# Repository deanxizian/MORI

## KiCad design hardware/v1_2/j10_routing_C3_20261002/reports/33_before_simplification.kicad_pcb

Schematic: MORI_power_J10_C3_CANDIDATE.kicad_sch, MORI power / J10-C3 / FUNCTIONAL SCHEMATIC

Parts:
C1, C20: 100n; C_0603_1608Metric
C2: 1u 25V; C_0603_1608Metric__P3_C2
C10: Panasonic EEU-FR1C102 1000uF 16V; CP_Radial_D10.0mm_P5.00mm__P2_C10__P3_C10__P5_C10
C21, C41: 10n; C_0603_1608Metric
C30: Panasonic EEU-FR1C102 1000uF 16V; CP_Radial_D10.0mm_P5.00mm__P3_C30__P5_C30
C40: 100n; C_0603_1608Metric__P5_C40
C60: 22u / 25V / X7R; C_1210_3225Metric__P3_C60__P3R1_C60
C61: 100n / 50V / X7R; C_0603_1608Metric__P5_C61
C62, C72: 100n / 50V / X7R; C_0603_1608Metric
C63: 22u / 25V / X7R; C_1210_3225Metric__P5_C63
C64, C66, C73, C76: 22u / 25V / X7R; C_1210_3225Metric
C65: 75p / 50V / C0G; C_0603_1608Metric__P5_C65
C70: 22u / 25V / X7R; C_1210_3225Metric__P3_C70
C71: 100n / 50V / X7R; C_0603_1608Metric__P5_C71
C74: 22u / 25V / X7R; C_1210_3225Metric__P3_C74
C75: 75p / 50V / C0G; C_0603_1608Metric__P3R1_C75
D1, D20, D90: BZT52H-C10,115; D_SOD-123F
D10: B540C-13-F; D_SMC__P3_D10__P5_D10
D30: B540C-13-F; D_SMC__P5_D30
D40: BZT52H-C10,115; D_SOD-123F__P5_D40
F60: 1A / 125V / very fast; Fuse_Littelfuse-NANO2-451_453
F70: 2A / 125V / very fast; Fuse_Littelfuse-NANO2-451_453__P5_F70
H1, H2, H3, H4: M2 mounting / POSITION TBD; MountingHole_2.2mm_M2
J1: PACK AFTER 6.3A FUSE; AMASS_XT30UPB-M_1x02_P5.0mm_Vertical__P3_J1
J2: WHEEL BUCK VIN; AMASS_XT30UPB-M_1x02_P5.0mm_Vertical__P3_J2__P5_J2
J3: WHEEL BUCK 9V RETURN; AMASS_XT30UPB-M_1x02_P5.0mm_Vertical__P3R1_J3
J4: HEAD BUCK VIN; AMASS_XT30UPB-M_1x02_P5.0mm_Vertical__P2_J4__P3_J4__P3R1_J4
J5: HEAD BUCK 6V RETURN; AMASS_XT30UPB-M_1x02_P5.0mm_Vertical__P2_J5__P3_J5__P5_J5
J6: BAT_MON SERVICE / DNP; AMASS_XT30UPB-M_1x02_P5.0mm_Vertical__P3_J6__P3R1_J6; not fitted
J7: S288 L; JST_XH_B3B-XH-A_1x03_P2.50mm_Vertical__P2_J7__P3_J7__P5_J7
J8: S288 R; JST_XH_B3B-XH-A_1x03_P2.50mm_Vertical__P2_J8__P5_J8
J9: SCS0009 CHAIN; JST_XH_B3B-XH-A_1x03_P2.50mm_Vertical__P5_J9
J10: MOTION CONTROL; JST_PH_S8B-PH-K_1x08_P2.00mm_Horizontal__C2_land1p50_finish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
J11: WHEEL DUMP 5R6 EXTERNAL; AMASS_XT30UPB-M_1x02_P5.0mm_Vertical__P5R5_DUMP
J12: HEAD DUMP 10R EXTERNAL; AMASS_XT30UPB-M_1x02_P5.0mm_Vertical__P2_J12__P5_J12__P5R5_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
J13: S288 DATA; JST_PH_B2B-PH-K_1x02_P2.00mm_Vertical__P4_PH_ANNULUS
J14: HEAD DATA; JST_PH_B3B-PH-K_1x03_P2.00mm_Vertical__P4_PH_ANNULUS
J15: CHARGE INTERLOCK; JST_PH_B2B-PH-K_1x02_P2.00mm_Vertical__P4_PH_ANNULUS__P3R1_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
J16: CHARGER RAW VBUS SENSE; JST_PH_B2B-PH-K_1x02_P2.00mm_Vertical__P4_PH_ANNULUS__P3R1_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
J17: MOTION 5V OUT / 1+ 2GND; JST_PH_B2B-PH-K_1x02_P2.00mm_Vertical__P4_PH_ANNULUS
J18: CAM 5V OUT / 1+ 2GND; JST_XH_B2B-XH-A_1x02_P2.50mm_Vertical
J19: REAR MASTER / 1RETURN 2GND; JST_PH_B2B-PH-K_1x02_P2.00mm_Vertical__P4_PH_ANNULUS__P5_J19
JP60: SERVICE OFF / OPEN=ON; PinHeader_1x02_P2.54mm_Vertical__P3_JP60__P3R1_JP60
JP70: SERVICE OFF / OPEN=ON; PinHeader_1x02_P2.54mm_Vertical__P5_JP70
L60, L70: 10uH / SRP7050TA-100M; Bourns_SRP7050TA_8p4_span_2p5_gap
Q1: AO4407A; SOIC-8_3.9x4.9mm_P1.27mm__P5_Q1
Q10, Q90: AO4407A; SOIC-8_3.9x4.9mm_P1.27mm
Q11: AO3400A; SOT-23__P5_Q11
Q20, Q31, Q40: AO3400A; SOT-23
Q30: AO4407A; SOIC-8_3.9x4.9mm_P1.27mm__P5_Q30
Q50: MMBT3904LT1G; SOT-23__P5_Q50
R1, R30, R91: 10k; R_0603_1608Metric
R2: WSL2512R0100FEA 10mR 1% 1W; R_2512_6332Metric
R3, R4: 0; R_0603_1608Metric
R10: 10k; R_0603_1608Metric__P5_R10
R11: 100; R_0603_1608Metric__P5_R11
R20, R24, R40, R44: 2.2k; R_0603_1608Metric
R21: 33.2k 0.1%; R_0603_1608Metric
R22: 10k 0.1%; R_0603_1608Metric__P5_R22
R23, R43: 1M 0.1%; R_0603_1608Metric
R25: 37.4k 0.1%; R_0603_1608Metric
R26, R42, R46: 10k 0.1%; R_0603_1608Metric
R31: 100; R_0603_1608Metric__P5_R31
R41: 16.5k 0.1%; R_0603_1608Metric
R45: 18.7k 0.1%; R_0603_1608Metric__P5_R45
R50, R52: 100k 0.1%; R_0603_1608Metric
R51, R53: 27k 0.1%; R_0603_1608Metric
R54: 10k; R_0603_1608Metric__P5_R54
R55: 47k; R_0603_1608Metric
R56: 100k; R_0603_1608Metric__P5_R56
R60, R70: 100k / 0.1%; R_0603_1608Metric
R61: 13.3k / 0.1%; R_0603_1608Metric
R71: 13.3k / 0.1%; R_0603_1608Metric__P3_R71
R90: 100k; R_0603_1608Metric
TP60: +5V_MOTION; TestPoint_Pad_D1.5mm__P3_TP60
TP61: GND; TestPoint_Pad_D1.5mm__P5_TP61
TP70: +5V_CAM; TestPoint_Pad_D1.5mm__P3R1_TP70
TP71: GND; TestPoint_Pad_D1.5mm__P5_TP71
U1: INA180A1IDBVR; SOT-23-5__P5_U1
U20: LM393BDR; SOIC-8_3.9x4.9mm_P1.27mm__P5_U20
U21: TL431BIDBZR; SOT-23
U40: LM393BDR; SOIC-8_3.9x4.9mm_P1.27mm__P5_U40
U41: TL431BIDBZR; SOT-23__P5_U41
U60, U70: TPS54302DDCR; TI_DDC0006A_TPS54302

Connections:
/+3V3: C1.1, J10.1, U1.5 (VS)
/+5V_CAM: C73.1, C74.1, C75.1, J18.1 (5V_OUT), L70.2, R70.1, TP70.1
/+5V_MOTION: C63.1, C64.1, C65.1, J17.1 (5V_OUT), L60.2, R60.1, TP60.1
/ARM_Q: J10.2, Q11.1, Q31.1, R54.1
/BAT_ADC: J10.5, R50.2, R51.1
/BAT_IN: Q1.5, Q1.6, Q1.7, Q1.8, Q90.5, Q90.6, Q90.7, Q90.8
/BAT_MON: C2.1, F60.1, F70.1, J2.2 (PLUS), J4.2 (PLUS), J6.2 (PLUS), R2.2, R4.1, R50.1
/BAT_REV: D1.1, Q1.1 (SOURCE PROTECTED OUTPUT), Q1.2, Q1.3, R2.1, R3.1
/C5_BOOT: C72.1, U70.6 (BOOT)
/C5_EN: JP70.1 (EN), U70.5 (EN)
/C5_FB: C75.2, R70.2, R71.1, U70.4 (FB)
/C5_SW: C72.2, L70.1, U70.2 (SW)
/C5_VIN: C70.1, C71.1, C76.1, F70.2, U70.3 (VIN)
/CHG_BASE: Q50.1 (B), R55.2, R56.1
/CHG_N: J10.4, J15.1, Q50.3 (C)
/CURRENT_ADC: J10.7, U1.1 (OUT)
/FAULT_N: J10.3, U20.7 (OUT2), U40.7 (OUT2)
/GND: C1.2, C2.2, C10.2, C20.2, C21.2, C30.2, C40.2, C41.2, C60.2, C61.2, C63.2, C64.2, C66.2, C70.2, C71.2, C73.2, C74.2, C76.2, D20.2, D40.2, J1.1 (MINUS), J2.1 (MINUS), J3.1 (MINUS), J4.1 (MINUS), J5.1 (MINUS), J6.1 (MINUS), J7.1 (GND), J8.1 (GND), J9.1 (GND), J10.8, J13.2, J14.2, J15.2, J16.2, J17.2 (GND), J18.2 (GND), J19.2, JP60.2 (GND), JP70.2 (GND), Q11.2, Q20.2, Q31.2, Q40.2, Q50.2 (E), R1.2, R22.2, R26.2, R42.2, R46.2, R51.2, R53.2, R54.2, R56.2, R61.2, R71.2, TP61.1, TP71.1, U1.2 (GND), U20.4 (GND), U21.3 (A), U40.4 (GND), U41.3 (A), U60.1 (GND), U70.1 (GND)
/H6_IN: D30.2, J5.2 (PLUS)
/H_BRAKE_GATE: D40.1, Q40.1, R43.1, R44.2, U40.1 (OUT1)
/H_BUS: J9.3 (BUS), J14.1
/H_DUMP_D: J12.1 (MINUS), Q40.3
/H_GATE: Q30.4, R30.1, R31.1
/H_GATE_LOW: Q31.3, R31.2
/H_OVSENSE: C41.1, R45.2, R46.1, U40.6 (IN2-)
/H_PRE: D30.1, Q30.1, Q30.2, Q30.3, R30.2
/H_REF: R40.2, U40.2 (IN1-), U40.5 (IN2+), U41.1 (K), U41.2 (REF)
/H_SENSE: R41.2, R42.1, R43.2, U40.3 (IN1+)
/H_VM: C30.1, C40.1, J9.2 (V+), J12.2 (PLUS), Q30.5 (DRAIN SWITCHED OUTPUT), Q30.6, Q30.7, Q30.8, R40.1, R41.1, R44.1, R45.1, U40.8 (VCC)
/KELVIN_N: R4.2, U1.4 (IN-)
/KELVIN_P: R3.2, U1.3 (IN+)
/M5_BOOT: C62.1, U60.6 (BOOT)
/M5_EN: JP60.1 (EN), U60.5 (EN)
/M5_FB: C65.2, R60.2, R61.1, U60.4 (FB)
/M5_SW: C62.2, L60.1, U60.2 (SW)
/M5_VIN: C60.1, C61.1, C66.1, F60.2, U60.3 (VIN)
/MASTER_GATE: D90.2, Q90.4, R90.2, R91.1
/MASTER_RETURN: J19.1, R91.2
/PACK_FUSED: D90.1, J1.2 (PLUS), Q90.1, Q90.2, Q90.3, R90.1
/REV_GATE: D1.2, Q1.4, R1.1
/VBUS_CHARGE: J16.1, R55.1
/W9_IN: D10.2, J3.2 (PLUS)
/WHEEL_ADC: J10.6, R52.2, R53.1
/W_BRAKE_GATE: D20.1, Q20.1, R23.1, R24.2, U20.1 (OUT1)
/W_BUS: J7.3 (BUS), J8.3 (BUS), J13.1
/W_DUMP_D: J11.1 (MINUS), Q20.3
/W_GATE: Q10.4, R10.1, R11.1
/W_GATE_LOW: Q11.3, R11.2
/W_OVSENSE: C21.1, R25.2, R26.1, U20.6 (IN2-)
/W_PRE: D10.1, Q10.1, Q10.2, Q10.3, R10.2
/W_REF: R20.2, U20.2 (IN1-), U20.5 (IN2+), U21.1 (K), U21.2 (REF)
/W_SENSE: R21.2, R22.1, R23.2, U20.3 (IN1+)
/W_VM: C10.1, C20.1, J7.2 (V+), J8.2 (V+), J11.2 (PLUS), Q10.5 (DRAIN SWITCHED OUTPUT), Q10.6, Q10.7, Q10.8, R20.1, R21.1, R24.1, R25.1, R52.1, U20.8 (VCC)

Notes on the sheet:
MORI / POWER CONDITIONER / P4
Power flows left to right. Supplies above, returns below. PROTOTYPE / UNVALIDATED.
01 Pack input / reverse protection / shunt
Q90 master stage precedes BAT_IN. No charger on this PCB.
10mR / 1% / 1W
02 Kelvin current sense
Sense from the shunt pads. Discharge-only nominal transfer: 0.2 V/A.
03 Wheel 9 V conditioning
External buck return. Inrush, brake energy and thermal performance: NOT_TESTED.
1000u / 16V
04 Head 6 V conditioning
05 External converter input distribution
J2: wheel buck. J4: head buck. J6: BAT_MON SERVICE / DNP.
06 Wheel rail / brake and overvoltage
Two comparators share one LM393B. External dump resistor needs pulse qualification.
LM393B / brake + fault
5R6 / 5W external
07 Head rail / brake and overvoltage
10R / 5W external
08 Voltage monitor / motion connector
Divider ratio 27 / 127. Current_ADC comes from block 02.
09 Charge insertion / VBUS sense
Sense and interlock only; no CC / PD / CC-CV charger implementation.
10 Supply boundaries / board mounting
80 x 55 mm PCB; populated assembly and thermal performance are not qualified.
Supply boundary
11 Motion 5 V / independent fused buck
Prototype: verify stability, temperature, cable drop and concurrent load. No PCB placement frozen.
1A input fuse
22u/25V
100n
100n BOOT
10uH / 4A rms
MOTION 5V
100k 0.1%
13.3k 0.1%
75p C0G
OPEN=ON / SHORT=OFF
5V probe
GND probe

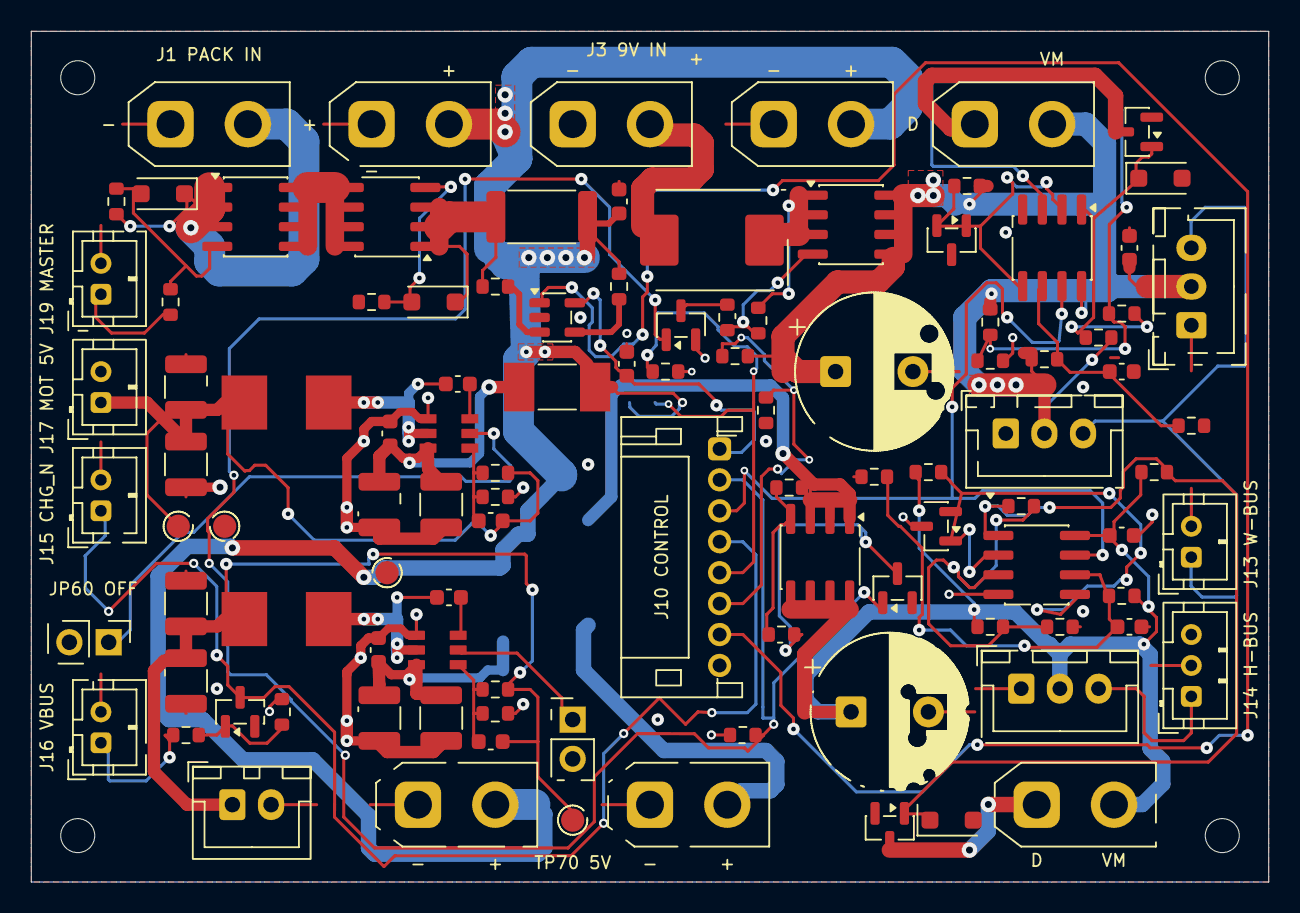
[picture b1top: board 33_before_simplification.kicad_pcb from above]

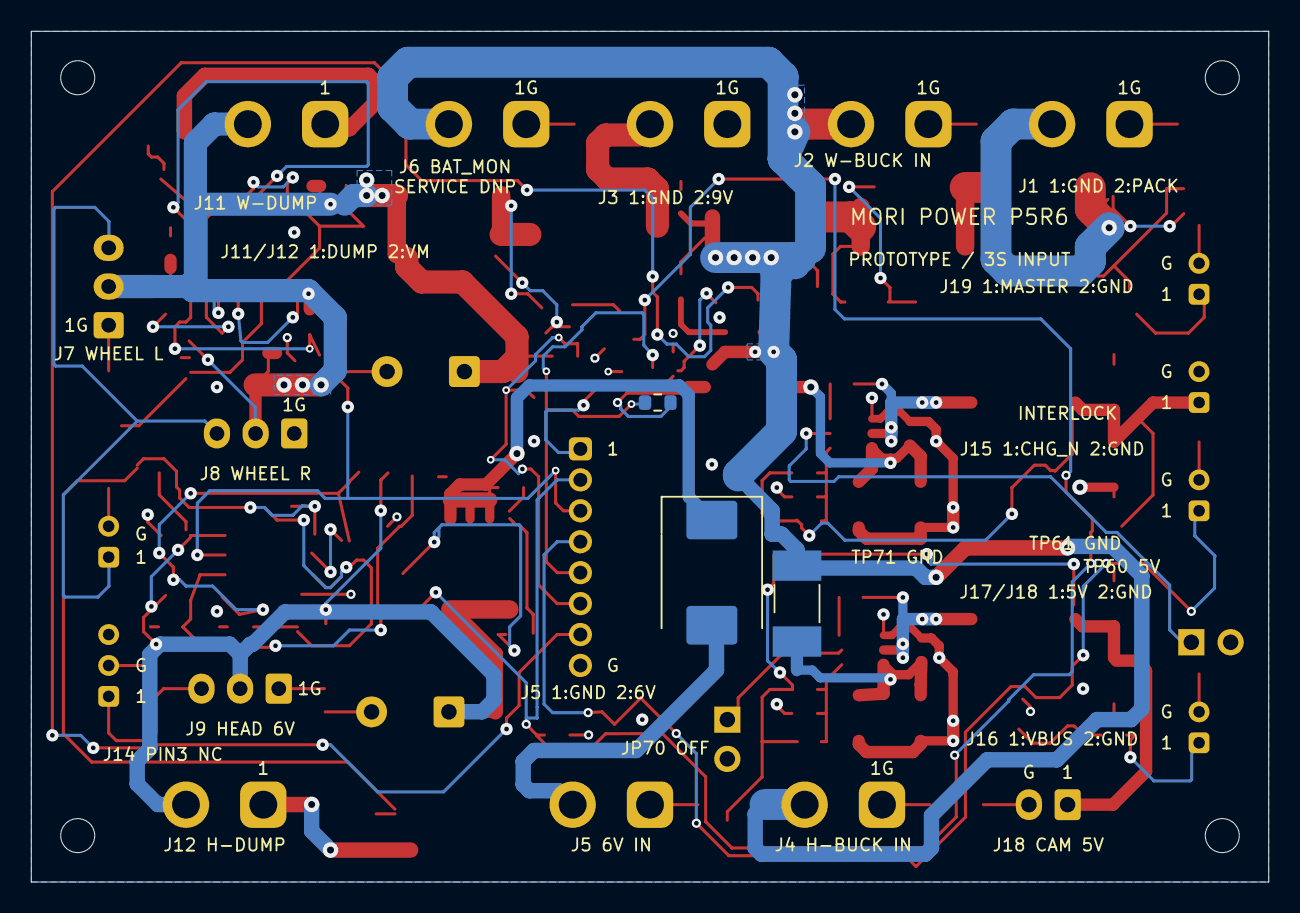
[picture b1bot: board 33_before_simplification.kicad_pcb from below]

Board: 4 copper layers, 80.0 x 55.0 mm, 112 parts (3 on the bottom side), 53 nets.

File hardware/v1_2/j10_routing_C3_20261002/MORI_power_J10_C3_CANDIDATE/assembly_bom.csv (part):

ref,value,footprint,source,note
J1,PACK AFTER 6.3A FUSE,MORI_Custom:AMASS_XT30UPB-M_1x02_P5.0mm_Vertical__P3_J1,,Protected finished3S pack through external6.3A fuse. On-board Q90 is controlled by rear SW1. No direct small-switch load current.
J2,WHEEL BUCK VIN,MORI_Custom:AMASS_XT30UPB-M_1x02_P5.0mm_Vertical__P3_J2__P5_J2,,"AMASS XT30UPB-M PCB: pin1 minus, pin2 plus; mating housing polarization plus continuity check mandatory."
J3,WHEEL BUCK 9V RETURN,MORI_Custom:AMASS_XT30UPB-M_1x02_P5.0mm_Vertical__P3R1_J3,,"AMASS XT30UPB-M PCB: pin1 minus, pin2 plus; mating housing polarization plus continuity check mandatory."
J4,HEAD BUCK VIN,MORI_Custom:AMASS_XT30UPB-M_1x02_P5.0mm_Vertical__P2_J4__P3_J4__P3R1_J4,,"AMASS XT30UPB-M PCB: pin1 minus, pin2 plus; mating housing polarization plus continuity check mandatory."
J5,HEAD BUCK 6V RETURN,MORI_Custom:AMASS_XT30UPB-M_1x02_P5.0mm_Vertical__P2_J5__P3_J5__P5_J5,,"AMASS XT30UPB-M PCB: pin1 minus, pin2 plus; mating housing polarization plus continuity check mandatory."
J6,BAT_MON SERVICE / DNP,MORI_Custom:AMASS_XT30UPB-M_1x02_P5.0mm_Vertical__P3_J6__P3R1_J6,,Legacy external5V feed no longer used. Not5V. Leave unpopulated in S3.
J11,WHEEL DUMP 5R6 EXTERNAL,MORI_Custom:AMASS_XT30UPB-M_1x02_P5.0mm_Vertical__P5R5_DUMP,,"AMASS XT30UPB-M PCB: pin1 minus, pin2 plus; mating housing polarization plus continuity check mandatory."
J12,HEAD DUMP 10R EXTERNAL,MORI_Custom:AMASS_XT30UPB-M_1x02_P5.0mm_Vertical__P2_J12__P5_J12__P5R5_DUMP,,"AMASS XT30UPB-M PCB: pin1 minus, pin2 plus; mating housing polarization plus continuity check mandatory."
J7,S288 L,MORI_Custom:JST_XH_B3B-XH-A_1x03_P2.50mm_Vertical__P2_J7__P3_J7__P5_J7,,Board-side XH 3-pin interface only. SCS original 5264-3P uses 1GND/2VCC/3TTL. S288 factory mating plug remains unverified; adapter harness must be confirmed.
J8,S288 R,MORI_Custom:JST_XH_B3B-XH-A_1x03_P2.50mm_Vertical__P2_J8__P5_J8,,Board-side XH 3-pin interface only. SCS original 5264-3P uses 1GND/2VCC/3TTL. S288 factory mating plug remains unverified; adapter harness must be confirmed.
J9,SCS0009 CHAIN,MORI_Custom:JST_XH_B3B-XH-A_1x03_P2.50mm_Vertical__P5_J9,,Board-side XH 3-pin interface only. SCS original 5264-3P uses 1GND/2VCC/3TTL. S288 factory mating plug remains unverified; adapter harness must be confirmed.
J10,MOTION CONTROL,Connector_JST:JST_PH_S8B-PH-K_1x08_P2.00mm_Horizontal__C2_land1p50_finished0p90,https://www.jst-mfg.com/product/pdf/eng/ePH.pdf,P4 PH 2.0 mm. PHR-8 / SPH-002T-P0.5S. Signal pin numbering unchanged. Check both mating views; never wire by color alone.
J13,S288 DATA,MORI_Custom:JST_PH_B2B-PH-K_1x02_P2.00mm_Vertical__P4_PH_ANNULUS,https://www.jst-mfg.com/product/pdf/eng/ePH.pdf,P4 PH 2.0 mm. PHR-2 / SPH-002T-P0.5S. Signal pin numbering unchanged. Check both mating views; never wire by color alone.
J14,HEAD DATA,MORI_Custom:JST_PH_B3B-PH-K_1x03_P2.00mm_Vertical__P4_PH_ANNULUS,https://www.jst-mfg.com/product/pdf/eng/ePH.pdf,P4 PH 2.0 mm. PHR-3 / SPH-002T-P0.5S. Signal pin numbering unchanged. Check both mating views; never wire by color alone.
J15,CHARGE INTERLOCK,MORI_Custom:JST_PH_B2B-PH-K_1x02_P2.00mm_Vertical__P4_PH_ANNULUS__P3R1_J15,https://www.jst-mfg.com/product/pdf/eng/ePH.pdf,P4 PH 2.0 mm. PHR-2 / SPH-002T-P0.5S. Signal pin numbering unchanged. Check both mating views; never wire by color alone.
J16,CHARGER RAW VBUS SENSE,MORI_Custom:JST_PH_B2B-PH-K_1x02_P2.00mm_Vertical__P4_PH_ANNULUS__P3R1_J16,https://www.jst-mfg.com/product/pdf/eng/ePH.pdf,P4 PH 2.0 mm. PHR-2 / SPH-002T-P0.5S. Signal pin numbering unchanged. Check both mating views; never wire by color alone.
Q1,AO4407A,MORI_Custom:SOIC-8_3.9x4.9mm_P1.27mm__P5_Q1,https://www.aosmd.com/sites/default/files/res/datasheets/AO4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,
R1,10k,Resistor_SMD:R_0603_1608Metric,,
D1,"BZT52H-C10,115",Diode_SMD:D_SOD-123F,,
R2,WSL2512R0100FEA 10mR 1% 1W,Resistor_SMD:R_2512_6332Metric,,
U1,INA180A1IDBVR,MORI_Custom:SOT-23-5__P5_U1,https://www.ti.com/lit/ds/symlink/ina180.pdf,Kelvin sense of 10mR; gain20 =>0.2V/A. Discharge only; reverse current not measured.
R3,0,Resistor_SMD:R_0603_1608Metric,,
R4,0,Resistor_SMD:R_0603_1608Metric,,
D10,B540C-13-F,MORI_Custom:D_SMC__P3_D10__P5_D10,https://www.diodes.com/datasheet/download/B540C.pdf,B540C-13-F verified from DS13012 Rev18-2; SMC cathode pin1. Thermal/quote NOT_QUALIFIED.
Q10,AO4407A,Package_SO:SOIC-8_3.9x4.9mm_P1.27mm,https://www.aosmd.com/sites/default/files/res/datasheets/AO4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,
Q11,AO3400A,MORI_Custom:SOT-23__P5_Q11,https://www.aosmd.com/sites/default/files/res/datasheets/AO3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,
R10,10k,MORI_Custom:R_0603_1608Metric__P5_R10,,
R11,100,MORI_Custom:R_0603_1608Metric__P5_R11,,
C10,Panasonic EEU-FR1C102 1000uF 16V,MORI_Custom:CP_Radial_D10.0mm_P5.00mm__P2_C10__P3_C10__P5_C10,,"D10 x H16; height is vendor capacitor envelope, NOT fitted into old10mm allocation."
D30,B540C-13-F,MORI_Custom:D_SMC__P5_D30,https://www.diodes.com/datasheet/download/B540C.pdf,B540C-13-F verified from DS13012 Rev18-2; SMC cathode pin1. Thermal/quote NOT_QUALIFIED.
Q30,AO4407A,MORI_Custom:SOIC-8_3.9x4.9mm_P1.27mm__P5_Q30,https://www.aosmd.com/sites/default/files/res/datasheets/AO4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,
Q31,AO3400A,Package_TO_SOT_SMD:SOT-23,https://www.aosmd.com/sites/default/files/res/datasheets/AO3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,
R30,10k,Resistor_SMD:R_0603_1608Metric,,
R31,100,MORI_Custom:R_0603_1608Metric__P5_R31,,
C30,Panasonic EEU-FR1C102 1000uF 16V,MORI_Custom:CP_Radial_D10.0mm_P5.00mm__P3_C30__P5_C30,,"D10 x H16; height is vendor capacitor envelope, NOT fitted into old10mm allocation."
U20,LM393BDR,MORI_Custom:SOIC-8_3.9x4.9mm_P1.27mm__P5_U20,https://www.ti.com/lit/ds/symlink/lm393b.pdf,
U21,TL431BIDBZR,Package_TO_SOT_SMD:SOT-23,https://www.ti.com/lit/ds/symlink/tl431.pdf,"DBZ pin1 cathode,2 reference,3 anode. B grade +/-0.5% at25C; thermal error in tolerance model."
Q20,AO3400A,Package_TO_SOT_SMD:SOT-23,https://www.aosmd.com/sites/default/files/res/datasheets/AO3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,
D20,"BZT52H-C10,115",Diode_SMD:D_SOD-123F,,
R20,2.2k,Resistor_SMD:R_0603_1608Metric,,
R21,33.2k 0.1%,Resistor_SMD:R_0603_1608Metric,,
R22,10k 0.1%,MORI_Custom:R_0603_1608Metric__P5_R22,,
R23,1M 0.1%,Resistor_SMD:R_0603_1608Metric,,
R24,2.2k,Resistor_SMD:R_0603_1608Metric,,
R25,37.4k 0.1%,Resistor_SMD:R_0603_1608Metric,,
R26,10k 0.1%,Resistor_SMD:R_0603_1608Metric,,
C20,100n,Capacitor_SMD:C_0603_1608Metric,,
C21,10n,Capacitor_SMD:C_0603_1608Metric,,
U40,LM393BDR,MORI_Custom:SOIC-8_3.9x4.9mm_P1.27mm__P5_U40,https://www.ti.com/lit/ds/symlink/lm393b.pdf,
U41,TL431BIDBZR,MORI_Custom:SOT-23__P5_U41,https://www.ti.com/lit/ds/symlink/tl431.pdf,"DBZ pin1 cathode,2 reference,3 anode. B grade +/-0.5% at25C; thermal error in tolerance model."
Q40,AO3400A,Package_TO_SOT_SMD:SOT-23,https://www.aosmd.com/sites/default/files/res/datasheets/AO3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,
D40,"BZT52H-C10,115",MORI_Custom:D_SOD-123F__P5_D40,,
R40,2.2k,Resistor_SMD:R_0603_1608Metric,,
R41,16.5k 0.1%,Resistor_SMD:R_0603_1608Metric,,
R42,10k 0.1%,Resistor_SMD:R_0603_1608Metric,,
R43,1M 0.1%,Resistor_SMD:R_0603_1608Metric,,
R44,2.2k,Resistor_SMD:R_0603_1608Metric,,
R45,18.7k 0.1%,MORI_Custom:R_0603_1608Metric__P5_R45,,
R46,10k 0.1%,Resistor_SMD:R_0603_1608Metric,,
C40,100n,MORI_Custom:C_0603_1608Metric__P5_C40,,
C41,10n,Capacitor_SMD:C_0603_1608Metric,,
R50,100k 0.1%,Resistor_SMD:R_0603_1608Metric,,
R51,27k 0.1%,Resistor_SMD:R_0603_1608Metric,,
R52,100k 0.1%,Resistor_SMD:R_0603_1608Metric,,
R53,27k 0.1%,Resistor_SMD:R_0603_1608Metric,,
R54,10k,MORI_Custom:R_0603_1608Metric__P5_R54,,
R55,47k,Resistor_SMD:R_0603_1608Metric,,
R56,100k,MORI_Custom:R_0603_1608Metric__P5_R56,,
C1,100n,Capacitor_SMD:C_0603_1608Metric,,
C2,1u 25V,MORI_Custom:C_0603_1608Metric__P3_C2,,
Q50,MMBT3904LT1G,MORI_Custom:SOT-23__P5_Q50,,SOT23 1B 2E 3C. Raw VBUS detect only; neither CC nor charging control.
H1,M2 mounting / POSITION TBD,MountingHole:MountingHole_2.2mm_M2,,
H2,M2 mounting / POSITION TBD,MountingHole:MountingHole_2.2mm_M2,,
H3,M2 mounting / POSITION TBD,MountingHole:MountingHole_2.2mm_M2,,
H4,M2 mounting / POSITION TBD,MountingHole:MountingHole_2.2mm_M2,,
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
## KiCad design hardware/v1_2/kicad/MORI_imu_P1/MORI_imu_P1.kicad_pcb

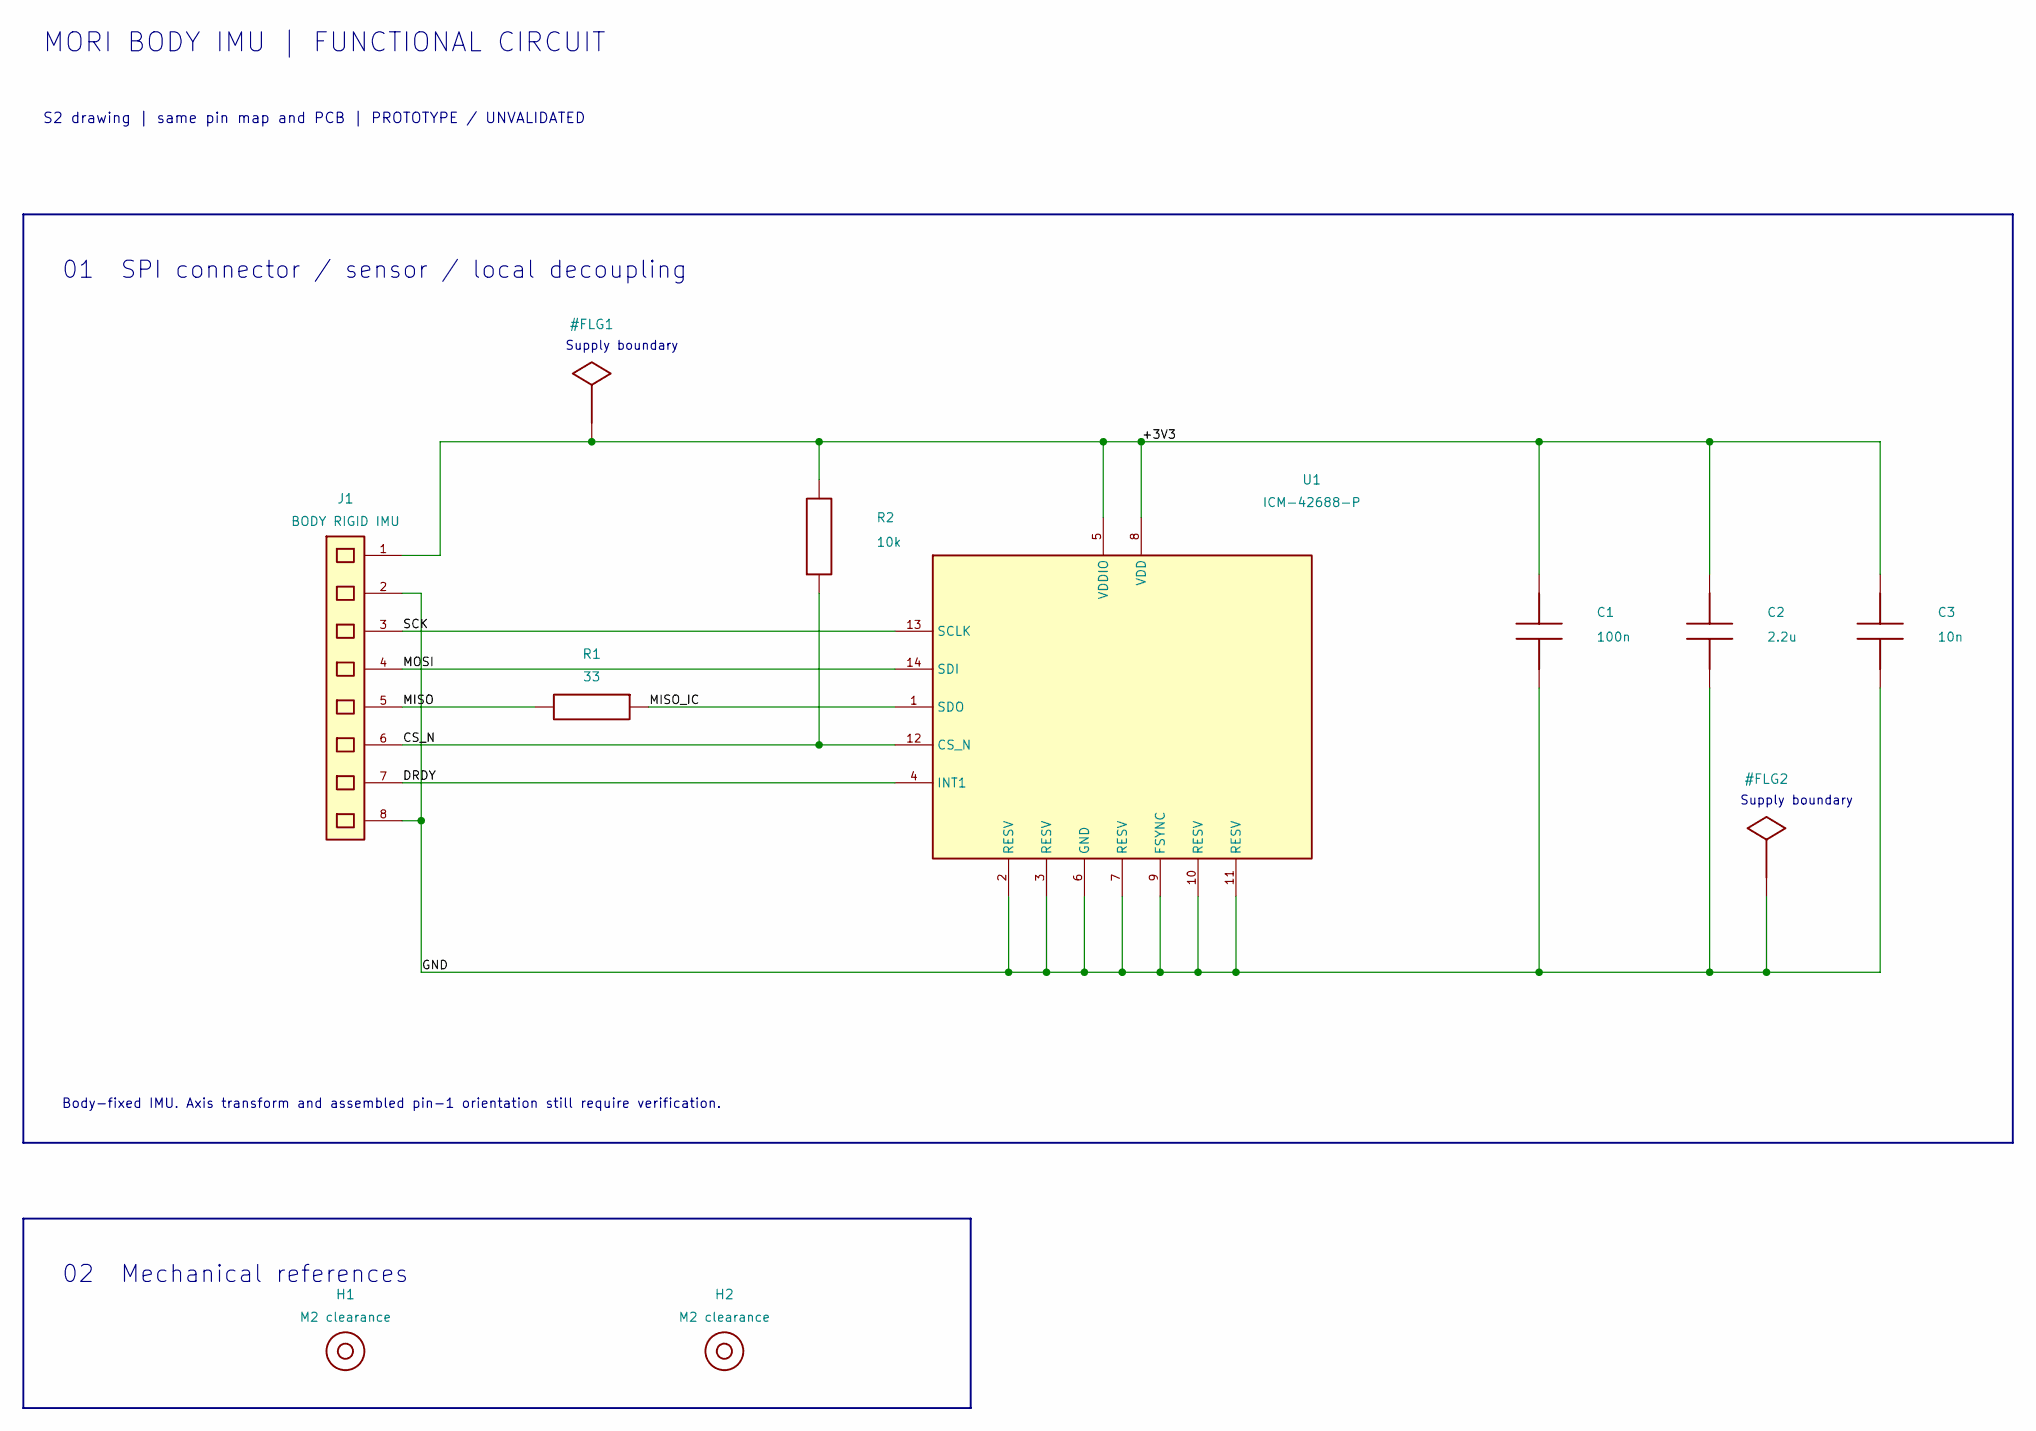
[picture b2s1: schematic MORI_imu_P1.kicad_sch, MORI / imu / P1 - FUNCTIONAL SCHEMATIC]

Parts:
C1: 100n; C_0603_1608Metric
C2: 2.2u; C_0603_1608Metric
C3: 10n; C_0603_1608Metric
H1, H2: M2 clearance; MountingHole_2.2mm_M2
J1: BODY RIGID IMU; JST_GH_BM08B-GHS-TBT_1x08-1MP_P1.25mm_Vertical
R1: 33; R_0603_1608Metric
R2: 10k; R_0603_1608Metric
U1: ICM-42688-P; LGA-14_3x2.5mm_P0.5mm_LayoutBorder3x4y

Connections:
/+3V3: C1.1, C2.1, C3.1, J1.1, R2.2, U1.5 (VDDIO), U1.8 (VDD)
/CS_N: J1.6, R2.1, U1.12 (CS_N)
/DRDY: J1.7, U1.4 (INT1)
/GND: C1.2, C2.2, C3.2, J1.2, J1.8, U1.2 (RESV), U1.3 (RESV), U1.6 (GND), U1.7 (RESV), U1.9 (FSYNC), U1.10 (RESV), U1.11 (RESV)
/MISO: J1.5, R1.2
/MISO_IC: R1.1, U1.1 (SDO)
/MOSI: J1.4, U1.14 (SDI)
/SCK: J1.3, U1.13 (SCLK)

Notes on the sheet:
MORI BODY IMU | FUNCTIONAL CIRCUIT
S2 drawing | same pin map and PCB | PROTOTYPE / UNVALIDATED
01 SPI connector / sensor / local decoupling
Body-fixed IMU. Axis transform and assembled pin-1 orientation still require verification.
Supply boundary
02 Mechanical references

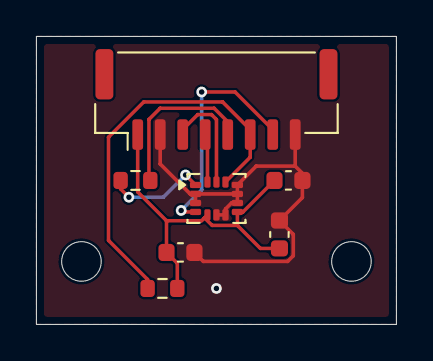
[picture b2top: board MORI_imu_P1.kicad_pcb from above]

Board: 2 copper layers, 20.0 x 16.0 mm, 9 parts (0 on the bottom side), 8 nets.

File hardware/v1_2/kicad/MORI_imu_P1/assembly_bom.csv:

ref,value,footprint,source,note
U1,ICM-42688-P,Package_LGA:LGA-14_3x2.5mm_P0.5mm_LayoutBorder3x4y,https://www.lcsc.com/datasheet/C1850418.pdf,Prototype based on vendor DS-000347 pinout. No raw cell welding; IC requires reflow. Assembly pad review required.
J1,BODY RIGID IMU,Connector_JST:JST_GH_BM08B-GHS-TBT_1x08-1MP_P1.25mm_Vertical,,Pin numbers are PCB connector numbers; harness mating view must be continuity checked.
C1,100n,Capacitor_SMD:C_0603_1608Metric,,
C2,2.2u,Capacitor_SMD:C_0603_1608Metric,,
C3,10n,Capacitor_SMD:C_0603_1608Metric,,
R1,33,Resistor_SMD:R_0603_1608Metric,,
R2,10k,Resistor_SMD:R_0603_1608Metric,,
H1,M2 clearance,MountingHole:MountingHole_2.2mm_M2,,
H2,M2 clearance,MountingHole:MountingHole_2.2mm_M2,,
